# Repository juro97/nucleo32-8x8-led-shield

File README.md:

# nucleo32-8x8-led-shield
Simple 8x8 led addon shield for nucleo32 boards. Tested on Nucleo32 L432KC.

Rows are driven through R1-R8, columns get switched by Q1-Q8, and there are two buttons (BTN1/BTN2) on board for input. Plugs straight onto the Nucleo32 headers.

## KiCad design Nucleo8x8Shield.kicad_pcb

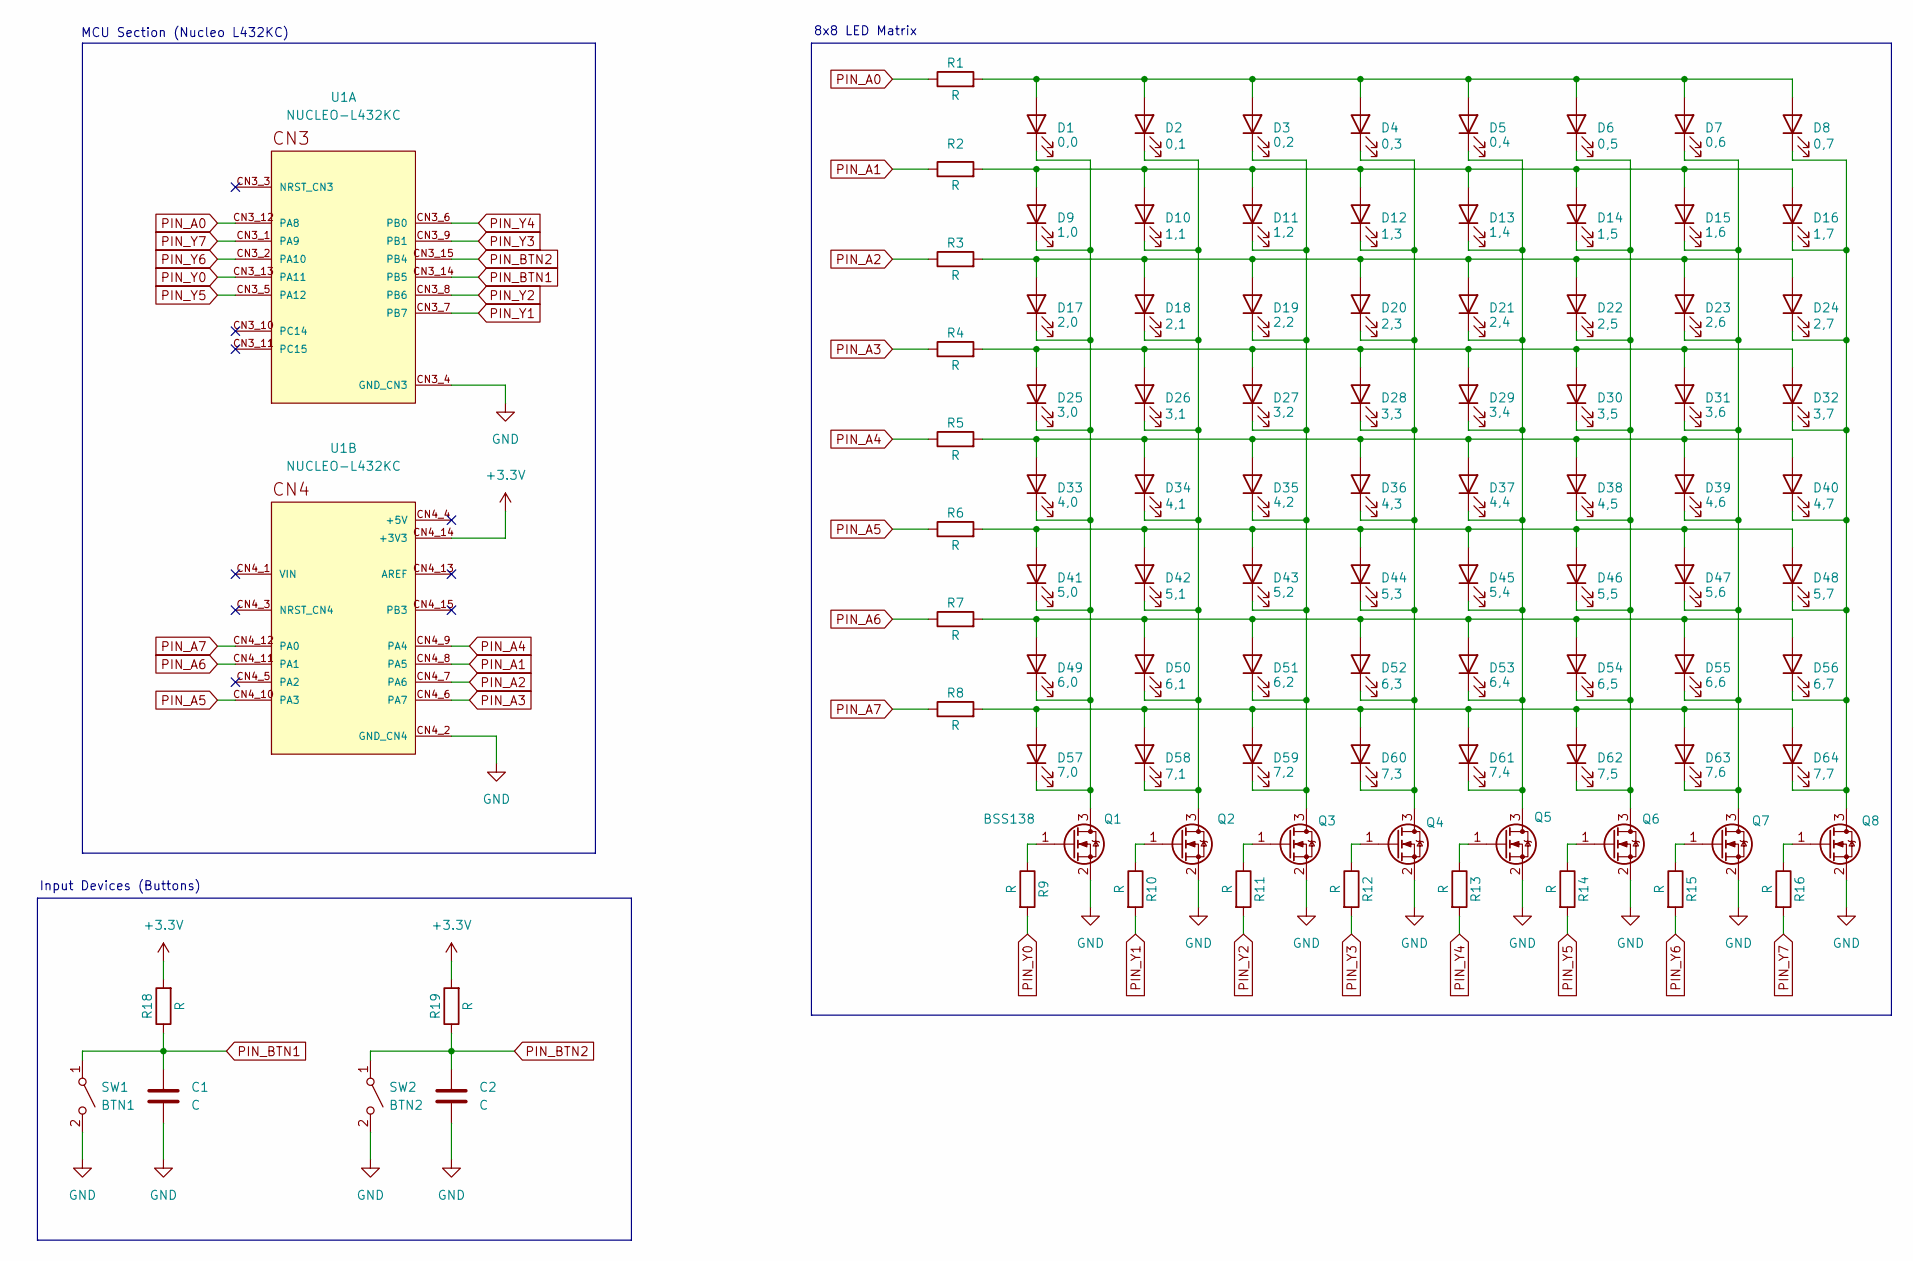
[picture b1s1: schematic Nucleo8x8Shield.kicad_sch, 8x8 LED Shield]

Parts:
C1, C2: C; C_0805_2012Metric_Pad1.18x1.45mm_HandSolder
D1: 0,0; LED_0805_2012Metric_Pad1.15x1.40mm_HandSolder
D2: 0,1; LED_0805_2012Metric_Pad1.15x1.40mm_HandSolder
D3: 0,2; LED_0805_2012Metric_Pad1.15x1.40mm_HandSolder
D4: 0,3; LED_0805_2012Metric_Pad1.15x1.40mm_HandSolder
D5: 0,4; LED_0805_2012Metric_Pad1.15x1.40mm_HandSolder
D6: 0,5; LED_0805_2012Metric_Pad1.15x1.40mm_HandSolder
D7: 0,6; LED_0805_2012Metric_Pad1.15x1.40mm_HandSolder
D8: 0,7; LED_0805_2012Metric_Pad1.15x1.40mm_HandSolder
D9: 1,0; LED_0805_2012Metric_Pad1.15x1.40mm_HandSolder
D10: 1,1; LED_0805_2012Metric_Pad1.15x1.40mm_HandSolder
D11: 1,2; LED_0805_2012Metric_Pad1.15x1.40mm_HandSolder
D12: 1,3; LED_0805_2012Metric_Pad1.15x1.40mm_HandSolder
D13: 1,4; LED_0805_2012Metric_Pad1.15x1.40mm_HandSolder
D14: 1,5; LED_0805_2012Metric_Pad1.15x1.40mm_HandSolder
D15: 1,6; LED_0805_2012Metric_Pad1.15x1.40mm_HandSolder
D16: 1,7; LED_0805_2012Metric_Pad1.15x1.40mm_HandSolder
D17: 2,0; LED_0805_2012Metric_Pad1.15x1.40mm_HandSolder
D18: 2,1; LED_0805_2012Metric_Pad1.15x1.40mm_HandSolder
D19: 2,2; LED_0805_2012Metric_Pad1.15x1.40mm_HandSolder
D20: 2,3; LED_0805_2012Metric_Pad1.15x1.40mm_HandSolder
D21: 2,4; LED_0805_2012Metric_Pad1.15x1.40mm_HandSolder
D22: 2,5; LED_0805_2012Metric_Pad1.15x1.40mm_HandSolder
D23: 2,6; LED_0805_2012Metric_Pad1.15x1.40mm_HandSolder
D24: 2,7; LED_0805_2012Metric_Pad1.15x1.40mm_HandSolder
D25: 3,0; LED_0805_2012Metric_Pad1.15x1.40mm_HandSolder
D26: 3,1; LED_0805_2012Metric_Pad1.15x1.40mm_HandSolder
D27: 3,2; LED_0805_2012Metric_Pad1.15x1.40mm_HandSolder
D28: 3,3; LED_0805_2012Metric_Pad1.15x1.40mm_HandSolder
D29: 3,4; LED_0805_2012Metric_Pad1.15x1.40mm_HandSolder
D30: 3,5; LED_0805_2012Metric_Pad1.15x1.40mm_HandSolder
D31: 3,6; LED_0805_2012Metric_Pad1.15x1.40mm_HandSolder
D32: 3,7; LED_0805_2012Metric_Pad1.15x1.40mm_HandSolder
D33: 4,0; LED_0805_2012Metric_Pad1.15x1.40mm_HandSolder
D34: 4,1; LED_0805_2012Metric_Pad1.15x1.40mm_HandSolder
D35: 4,2; LED_0805_2012Metric_Pad1.15x1.40mm_HandSolder
D36: 4,3; LED_0805_2012Metric_Pad1.15x1.40mm_HandSolder
D37: 4,4; LED_0805_2012Metric_Pad1.15x1.40mm_HandSolder
D38: 4,5; LED_0805_2012Metric_Pad1.15x1.40mm_HandSolder
D39: 4,6; LED_0805_2012Metric_Pad1.15x1.40mm_HandSolder
D40: 4,7; LED_0805_2012Metric_Pad1.15x1.40mm_HandSolder
D41: 5,0; LED_0805_2012Metric_Pad1.15x1.40mm_HandSolder
D42: 5,1; LED_0805_2012Metric_Pad1.15x1.40mm_HandSolder
D43: 5,2; LED_0805_2012Metric_Pad1.15x1.40mm_HandSolder
D44: 5,3; LED_0805_2012Metric_Pad1.15x1.40mm_HandSolder
D45: 5,4; LED_0805_2012Metric_Pad1.15x1.40mm_HandSolder
D46: 5,5; LED_0805_2012Metric_Pad1.15x1.40mm_HandSolder
D47: 5,6; LED_0805_2012Metric_Pad1.15x1.40mm_HandSolder
D48: 5,7; LED_0805_2012Metric_Pad1.15x1.40mm_HandSolder
D49: 6,0; LED_0805_2012Metric_Pad1.15x1.40mm_HandSolder
D50: 6,1; LED_0805_2012Metric_Pad1.15x1.40mm_HandSolder
D51: 6,2; LED_0805_2012Metric_Pad1.15x1.40mm_HandSolder
D52: 6,3; LED_0805_2012Metric_Pad1.15x1.40mm_HandSolder
D53: 6,4; LED_0805_2012Metric_Pad1.15x1.40mm_HandSolder
D54: 6,5; LED_0805_2012Metric_Pad1.15x1.40mm_HandSolder
D55: 6,6; LED_0805_2012Metric_Pad1.15x1.40mm_HandSolder
D56: 6,7; LED_0805_2012Metric_Pad1.15x1.40mm_HandSolder
D57: 7,0; LED_0805_2012Metric_Pad1.15x1.40mm_HandSolder
D58: 7,1; LED_0805_2012Metric_Pad1.15x1.40mm_HandSolder
D59: 7,2; LED_0805_2012Metric_Pad1.15x1.40mm_HandSolder
D60: 7,3; LED_0805_2012Metric_Pad1.15x1.40mm_HandSolder
D61: 7,4; LED_0805_2012Metric_Pad1.15x1.40mm_HandSolder
D62: 7,5; LED_0805_2012Metric_Pad1.15x1.40mm_HandSolder
D63: 7,6; LED_0805_2012Metric_Pad1.15x1.40mm_HandSolder
D64: 7,7; LED_0805_2012Metric_Pad1.15x1.40mm_HandSolder
Q1, Q2, Q3, Q4, Q5, Q6, Q7, Q8: BSS138; SOT-23
R1, R2, R3, R4, R5, R6, R7, R8, R9, R10, R11, R12, R13, R14, R15, R16, R18, R19: R; R_0805_2012Metric_Pad1.20x1.40mm_HandSolder
SW1: BTN1; SW_SPST_B3S-1000
SW2: BTN2; SW_SPST_B3S-1000
U1: NUCLEO-L432KC; MODULE_NUCLEO-L432KC; PARTREV N/A

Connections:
+3.3V: R18.2, R19.2, U1.CN4_14 (+3V3)
GND: C1.2, C2.2, Q1.2 (S), Q2.2 (S), Q3.2 (S), Q4.2 (S), Q5.2 (S), Q6.2 (S), Q7.2 (S), Q8.2 (S), SW1.2 (B), SW2.2 (B), U1.CN3_4 (GND_CN3), U1.CN4_2 (GND_CN4)
unnamed: D1.2 (A), D2.2 (A), D3.2 (A), D4.2 (A), D5.2 (A), D6.2 (A), D7.2 (A), D8.2 (A), R1.2
unnamed: D1.1 (K), D9.1 (K), D17.1 (K), D25.1 (K), D33.1 (K), D41.1 (K), D49.1 (K), D57.1 (K), Q1.3 (D)
unnamed: D9.2 (A), D10.2 (A), D11.2 (A), D12.2 (A), D13.2 (A), D14.2 (A), D15.2 (A), D16.2 (A), R2.2
unnamed: D2.1 (K), D10.1 (K), D18.1 (K), D26.1 (K), D34.1 (K), D42.1 (K), D50.1 (K), D58.1 (K), Q2.3 (D)
unnamed: D3.1 (K), D11.1 (K), D19.1 (K), D27.1 (K), D35.1 (K), D43.1 (K), D51.1 (K), D59.1 (K), Q3.3 (D)
unnamed: D4.1 (K), D12.1 (K), D20.1 (K), D28.1 (K), D36.1 (K), D44.1 (K), D52.1 (K), D60.1 (K), Q4.3 (D)
unnamed: D5.1 (K), D13.1 (K), D21.1 (K), D29.1 (K), D37.1 (K), D45.1 (K), D53.1 (K), D61.1 (K), Q5.3 (D)
unnamed: D6.1 (K), D14.1 (K), D22.1 (K), D30.1 (K), D38.1 (K), D46.1 (K), D54.1 (K), D62.1 (K), Q6.3 (D)
unnamed: D7.1 (K), D15.1 (K), D23.1 (K), D31.1 (K), D39.1 (K), D47.1 (K), D55.1 (K), D63.1 (K), Q7.3 (D)
unnamed: D8.1 (K), D16.1 (K), D24.1 (K), D32.1 (K), D40.1 (K), D48.1 (K), D56.1 (K), D64.1 (K), Q8.3 (D)
unnamed: D17.2 (A), D18.2 (A), D19.2 (A), D20.2 (A), D21.2 (A), D22.2 (A), D23.2 (A), D24.2 (A), R3.2
unnamed: D25.2 (A), D26.2 (A), D27.2 (A), D28.2 (A), D29.2 (A), D30.2 (A), D31.2 (A), D32.2 (A), R4.2
unnamed: D33.2 (A), D34.2 (A), D35.2 (A), D36.2 (A), D37.2 (A), D38.2 (A), D39.2 (A), D40.2 (A), R5.2
unnamed: D41.2 (A), D42.2 (A), D43.2 (A), D44.2 (A), D45.2 (A), D46.2 (A), D47.2 (A), D48.2 (A), R6.2
unnamed: D49.2 (A), D50.2 (A), D51.2 (A), D52.2 (A), D53.2 (A), D54.2 (A), D55.2 (A), D56.2 (A), R7.2
unnamed: D57.2 (A), D58.2 (A), D59.2 (A), D60.2 (A), D61.2 (A), D62.2 (A), D63.2 (A), D64.2 (A), R8.2
unnamed: Q1.1 (G), R9.1
unnamed: Q2.1 (G), R10.1
unnamed: Q3.1 (G), R11.1
unnamed: Q4.1 (G), R12.1
unnamed: Q5.1 (G), R13.1
unnamed: Q6.1 (G), R14.1
unnamed: Q7.1 (G), R15.1
unnamed: Q8.1 (G), R16.1
PIN_A0: R1.1, U1.CN3_12 (PA8)
PIN_A1: R2.1, U1.CN4_8 (PA5)
PIN_A2: R3.1, U1.CN4_7 (PA6)
PIN_A3: R4.1, U1.CN4_6 (PA7)
PIN_A4: R5.1, U1.CN4_9 (PA4)
PIN_A5: R6.1, U1.CN4_10 (PA3)
PIN_A6: R7.1, U1.CN4_11 (PA1)
PIN_A7: R8.1, U1.CN4_12 (PA0)
PIN_BTN1: C1.1, R18.1, SW1.1 (A), U1.CN3_14 (PB5)
PIN_BTN2: C2.1, R19.1, SW2.1 (A), U1.CN3_15 (PB4)
PIN_Y0: R9.2, U1.CN3_13 (PA11)
PIN_Y1: R10.2, U1.CN3_7 (PB7)
PIN_Y2: R11.2, U1.CN3_8 (PB6)
PIN_Y3: R12.2, U1.CN3_9 (PB1)
PIN_Y4: R13.2, U1.CN3_6 (PB0)
PIN_Y5: R14.2, U1.CN3_5 (PA12)
PIN_Y6: R15.2, U1.CN3_2 (PA10)
PIN_Y7: R16.2, U1.CN3_1 (PA9)

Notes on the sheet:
Input Devices (Buttons)
MCU Section (Nucleo L432KC)
8x8 LED Matrix

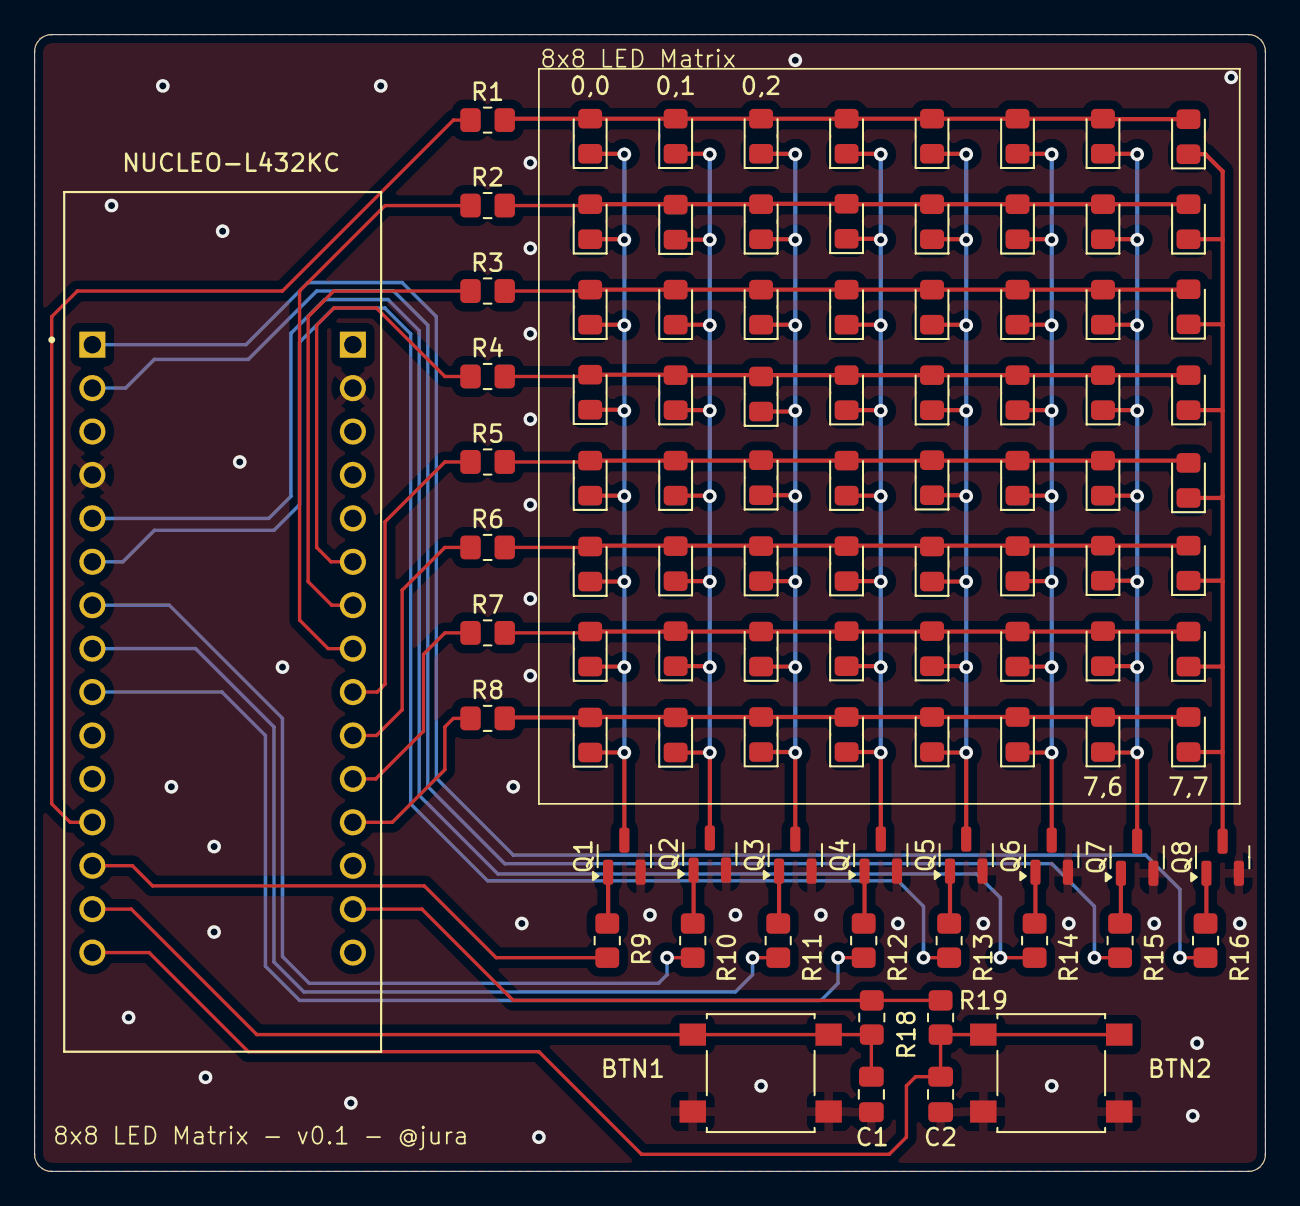
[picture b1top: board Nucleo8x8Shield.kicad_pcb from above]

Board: 2 copper layers, 72.0 x 66.5 mm, 95 parts (0 on the bottom side), 44 nets.
